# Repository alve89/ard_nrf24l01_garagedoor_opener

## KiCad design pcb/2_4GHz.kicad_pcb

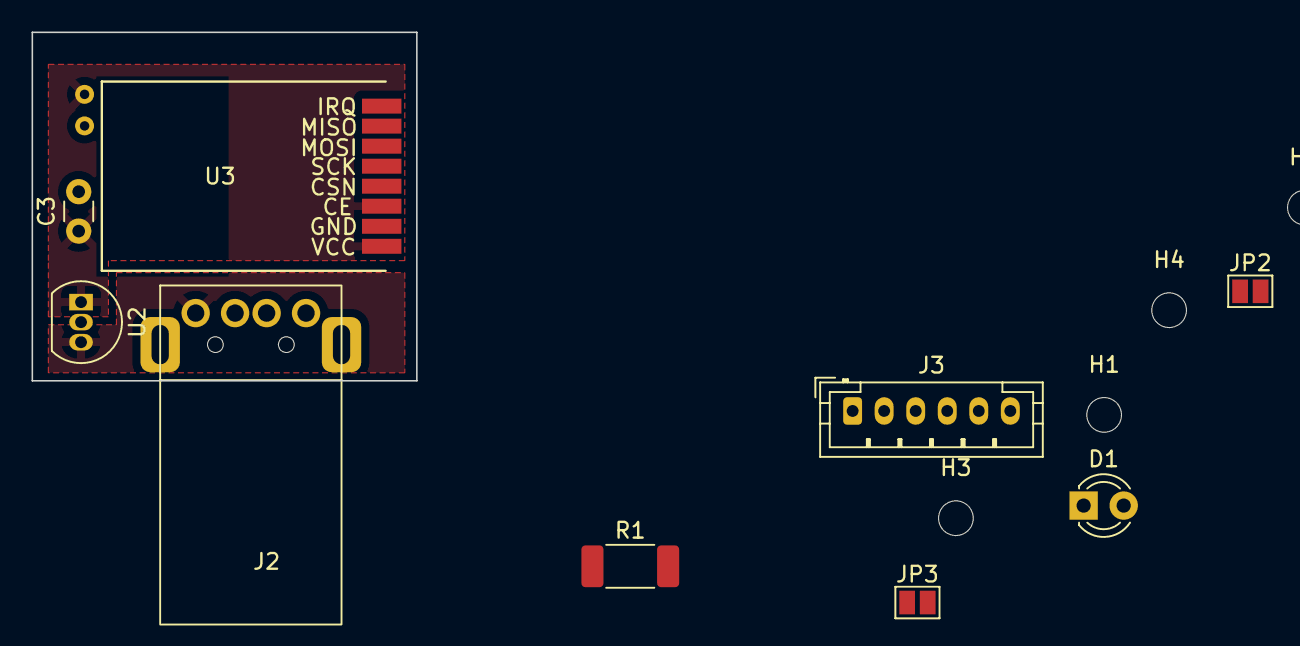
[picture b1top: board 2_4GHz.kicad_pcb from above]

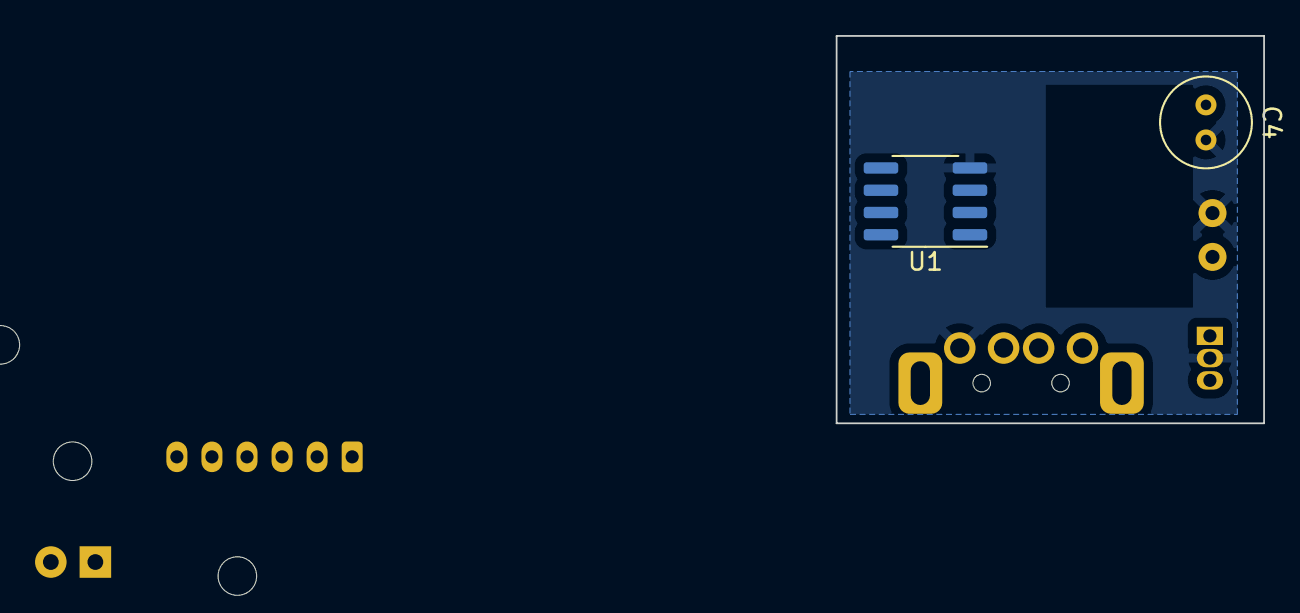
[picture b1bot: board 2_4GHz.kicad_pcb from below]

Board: 2 copper layers, 24.4 x 22.1 mm, 15 parts (2 on the bottom side), 11 nets, no tracks yet.

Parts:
C3: C; C_Disc_D3.0mm_W1.6mm_P2.50mm
C4: C_Polarized; C_Radial_D5.0mm_H5.0mm_P2.00mm
D1: LED; LED_D3.0mm
H1, H2, H3, H4: MountingHole; MountingHole_2.2mm_M2
J2: USB_A; USB_A_AliExpress_horizontal_male
J3: Conn_01x06_Male; JST_PH_B6B-PH-K_1x06_P2.00mm_Vertical
JP2, JP3: SolderJumper_2_Open; SolderJumper-2_P1.3mm_Open_Pad1.0x1.5mm
R1: R; R_2010_5025Metric_Pad1.40x2.65mm_HandSolder
U1: ATtiny85-20P; SOP-8_3.76x4.96mm_P1.27mm
U2: LP2950-3.3_TO92; TO-92_Inline
U3: NRF24L01_Breakout_8P; NRF24L01-Module-SMD

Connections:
/3V3: C3.1, C4.1, U2.1 (VO), U3.1 (VCC), U3.3 (CE)
/5V: J2.1 (VBUS), J3.5, U1.8 (VCC), U2.3 (VI)
/GND: C3.2, C4.2, J2.4 (GND), J3.6, JP2.1 (A), JP3.1 (A), R1.2, U1.4 (GND), U2.2 (GND), U3.2 (GND)
CSN: U1.2 (XTAL1/PB3), U3.4 (~CSN)
MISO: J3.3, U1.5 (AREF/PB0), U3.7 (MISO)
MOSI: J3.2, U1.6 (PB1), U3.6 (MOSI)
unnamed: D1.1 (K), R1.1
unnamed: J2.5 (Shield), JP2.2 (B)
unnamed: D1.2 (A), U1.3 (XTAL2/PB4)
RESET: J3.4, JP3.2 (B), U1.1 (~RESET/PB5)
SCK: J3.1, U1.7 (PB2), U3.5 (SCK)

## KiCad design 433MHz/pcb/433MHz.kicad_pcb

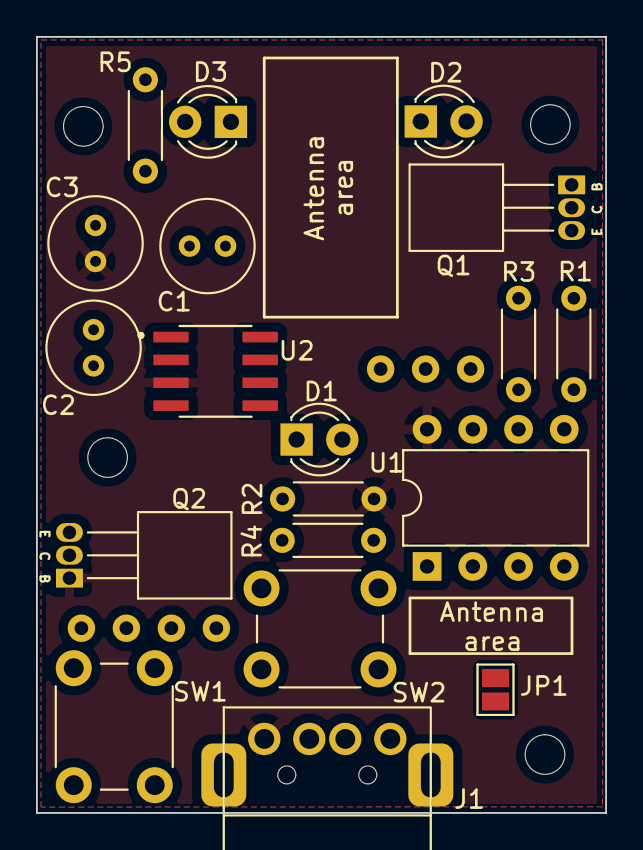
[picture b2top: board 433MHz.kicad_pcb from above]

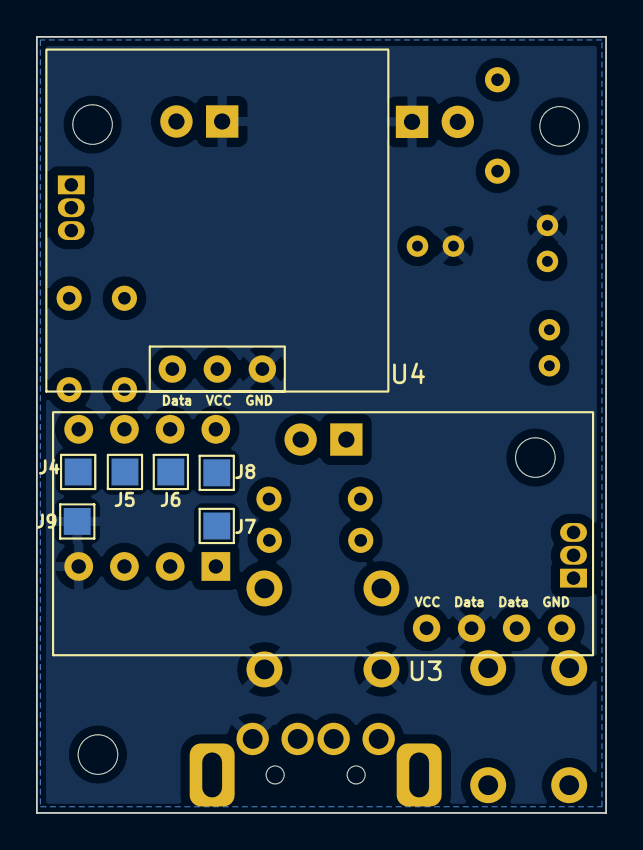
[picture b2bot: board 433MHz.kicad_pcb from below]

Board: 2 copper layers, 31.6 x 43.1 mm, 31 parts (8 on the bottom side), 19 nets, no tracks yet.

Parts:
C1, C2, C3: 1 uF; C_Radial_D5.0mm_H7.0mm_P2.00mm
D1, D2, D3: LED; LED_D3.0mm
H1, H2, H3, H4: MountingHole; MountingHole_2.2mm_M2
J1: USB_A; USB_A_AliExpress_horizontal_male
J4, J5, J6, J7, J8, J9: Conn_01x01_Male; TestPoint_Pad_1.5x1.5mm
JP1: SolderJumper_2_Open; SolderJumper-2_P1.3mm_Open_Pad1.0x1.5mm
Q1, Q2: Q_PNP_ECB; TO-92_Inline_Horizontal1
R1, R2, R3, R4, R5: R; R_Axial_DIN0204_L3.6mm_D1.6mm_P5.08mm_Horizontal
SW1: BUTTON_RESET; SW_PUSH_6mm_H7.3mm
SW2: BUTTON_SEND_DATA; SW_PUSH_6mm_H5mm
U1: ATtiny85-20P; DIP-8_W7.62mm
U2: MAX1681ESA; SOIC127P600X175-8N
U3: 433_MHz_Module_Receiver; 433MHz_Modul_Receiver
U4: 433_MHz_Module_Transmitter; 433MHz_Modul_Transmitter

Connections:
5V: C3.1, J1.1 (VBUS), J8.1, Q2.1 (E), R2.1, U1.8 (VCC), U2.3 (GND)
10V: C1.1, Q1.1 (E), U2.8 (IN)
DAT_RECEIVER: U1.7 (PB2), U3.4 (Data)
DAT_TRANSMITTER: U1.5 (AREF/PB0), U4.1 (GND)
GND: C1.2, C3.2, D2.1 (K), D3.1 (K), J1.4 (GND), J9.1, JP1.1 (A), SW2.2, U1.4 (GND), U2.1 (FSEL), U2.5 (OUT), U2.6 (LV), U2.7 (SHDN), U3.2 (GND), U4.3 (Data)
unnamed: C2.1, U2.2 (CAP+)
unnamed: C2.2, U2.4 (CAP-)
unnamed: D1.1 (K), SW2.1, U1.3 (XTAL2/PB4)
unnamed: D1.2 (A), R2.2
unnamed: D2.2 (A), R3.1
unnamed: D3.2 (A), R5.1
unnamed: J1.5 (Shield), JP1.2 (B)
unnamed: Q1.2 (C), U4.2 (VCC)
unnamed: Q1.3 (B), R1.1
unnamed: Q2.2 (C), U3.1 (VCC)
unnamed: Q2.3 (B), R4.1
unnamed: SW1.1, SW1.2, U1.1 (~RESET/PB5)
RECEIVER_POWER: R4.2, R5.2, U1.2 (XTAL1/PB3)
TRANSMITTER_POWER: R1.2, R3.2, U1.6 (PB1)

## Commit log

2023-07-12 Init repo
2023-07-12 Move PCB data to sub-directory
2023-07-12 Remove duplicate code file
2023-10-21 Add 433 MHz files
2023-10-23 Fixing logic of LDR sensor
2023-10-23 Improving reset() function
2023-10-23 Fixing several bugs
2023-10-25 Adding status LEDs
2023-10-26 Update PCB to Arduino UNO and Nano
2023-10-26 Remove autosave
2023-10-26 NRF works on Nano with PA_MAX power now
2023-10-27 Adding Ethernet and MQTT
2023-10-28 Added MQTT sensor for raw text
2023-10-29 Fixing logic, working!
2023-10-29 Fix of last commit
2023-10-29 Normal process successfully tested (leave, arrive)
2023-10-30 Almost working except of STOP!
2023-10-30 Adding todo
2023-10-30 Testing workflow
2023-10-30 Add todo
2023-11-13 Implement extended trigger information
2023-11-13 Edit github workflows
2023-11-13 Test edit for new workflow
2023-11-13 Re-edit workflows
2023-11-13 Edit for updated workflow
2023-11-15 Add logs for button + key, remove function of both
2023-11-15 Create classes - working - testing necessary
2023-11-17 Add test
2023-11-19 Fix problem with garage is not reacting
2023-11-24 Add new functions and button logging
2023-11-28 Add reboot reasons and ethernet reconnect
2023-12-20 Add logging
2024-01-31 Change relay-pin to inverted state
2024-02-08 Add version information
2024-02-09 Initial design
2024-02-09 Changed relay to module-type
2024-02-09 Fix relay trigger level issue
2024-02-09 Add OTA functionality
2024-02-09 Remove unnecessary MQTT entities
2024-02-09 Add reboot functionality (see #7)
2024-02-10 Further dev
2024-02-10 v1 finalized and ordered as prototype
2024-07-02 Adding Python code
